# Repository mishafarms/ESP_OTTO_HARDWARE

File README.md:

# OttoDIYESPShield
ESP32 hardware designs for OttoDIY

NOTICE: Most of this has now been verified and works ...

I have created a fusion 360 Otto that has the proper holes in the head for this PCB, I am also including the STL files.
the legs have been modified to use the servos and horns I have.

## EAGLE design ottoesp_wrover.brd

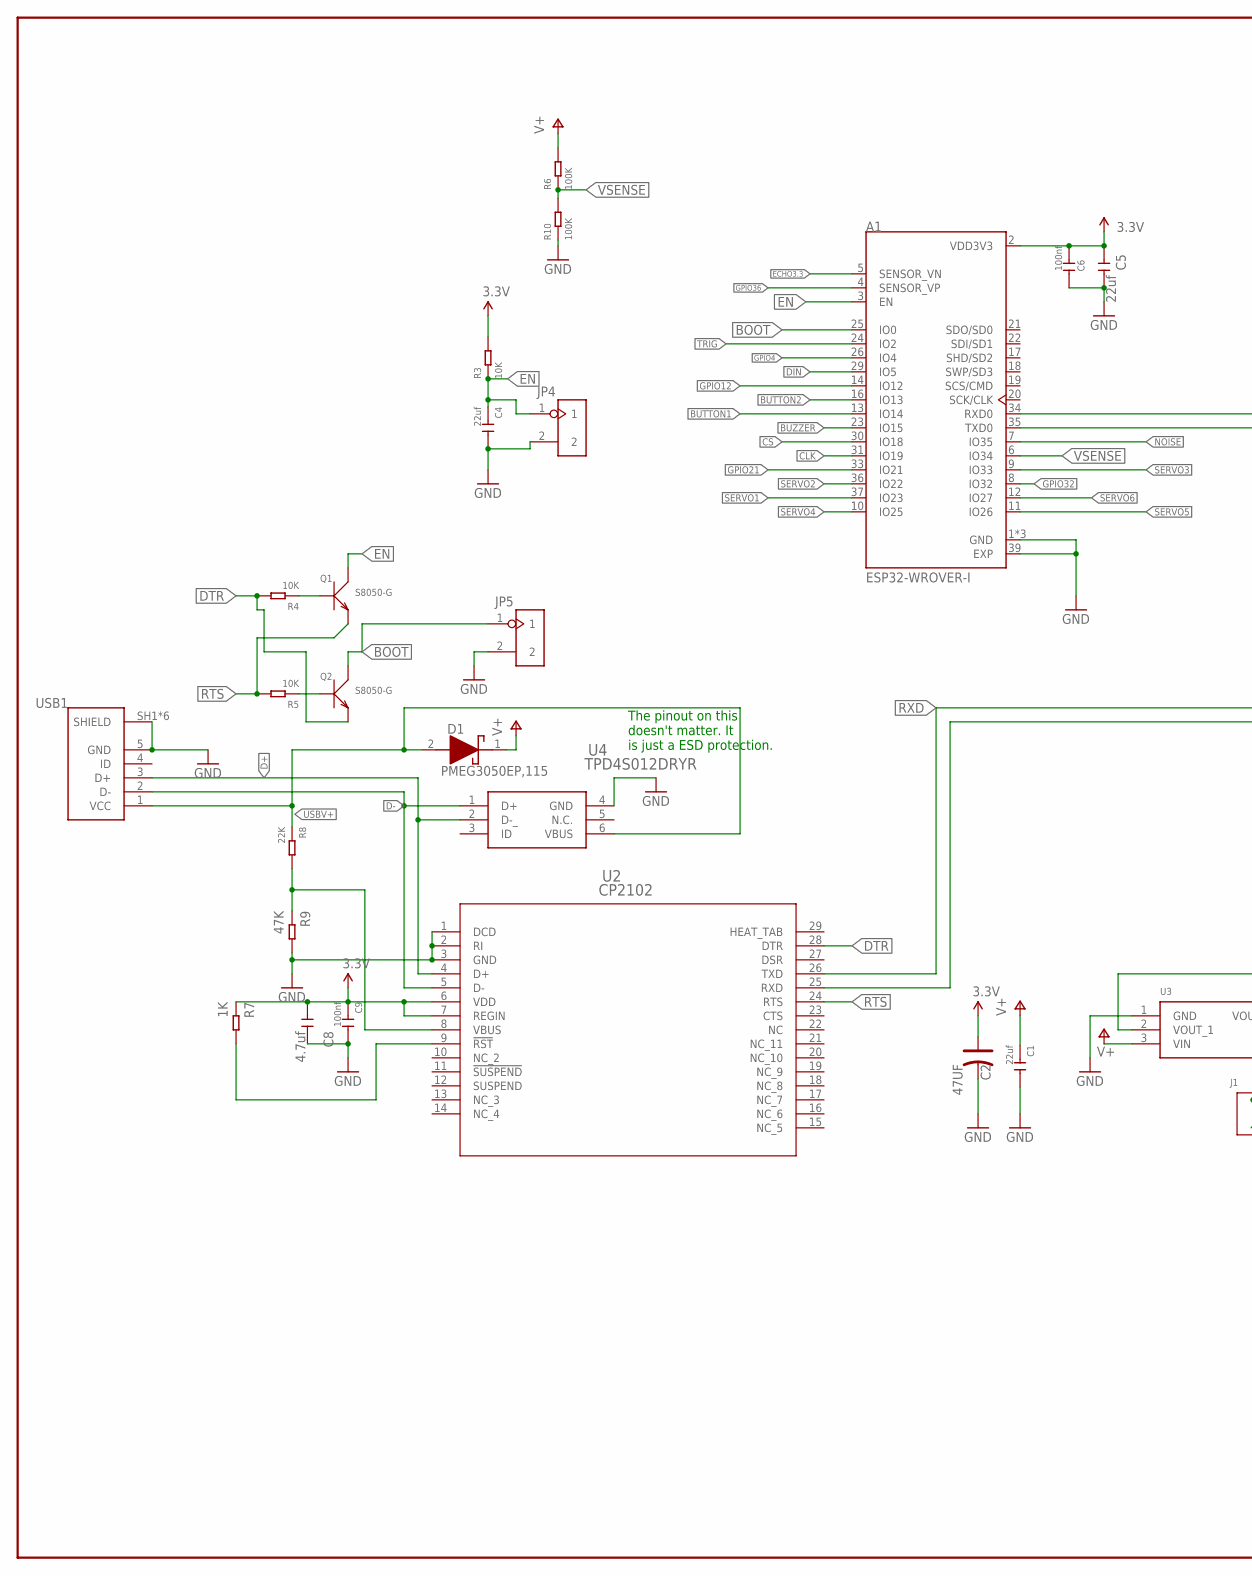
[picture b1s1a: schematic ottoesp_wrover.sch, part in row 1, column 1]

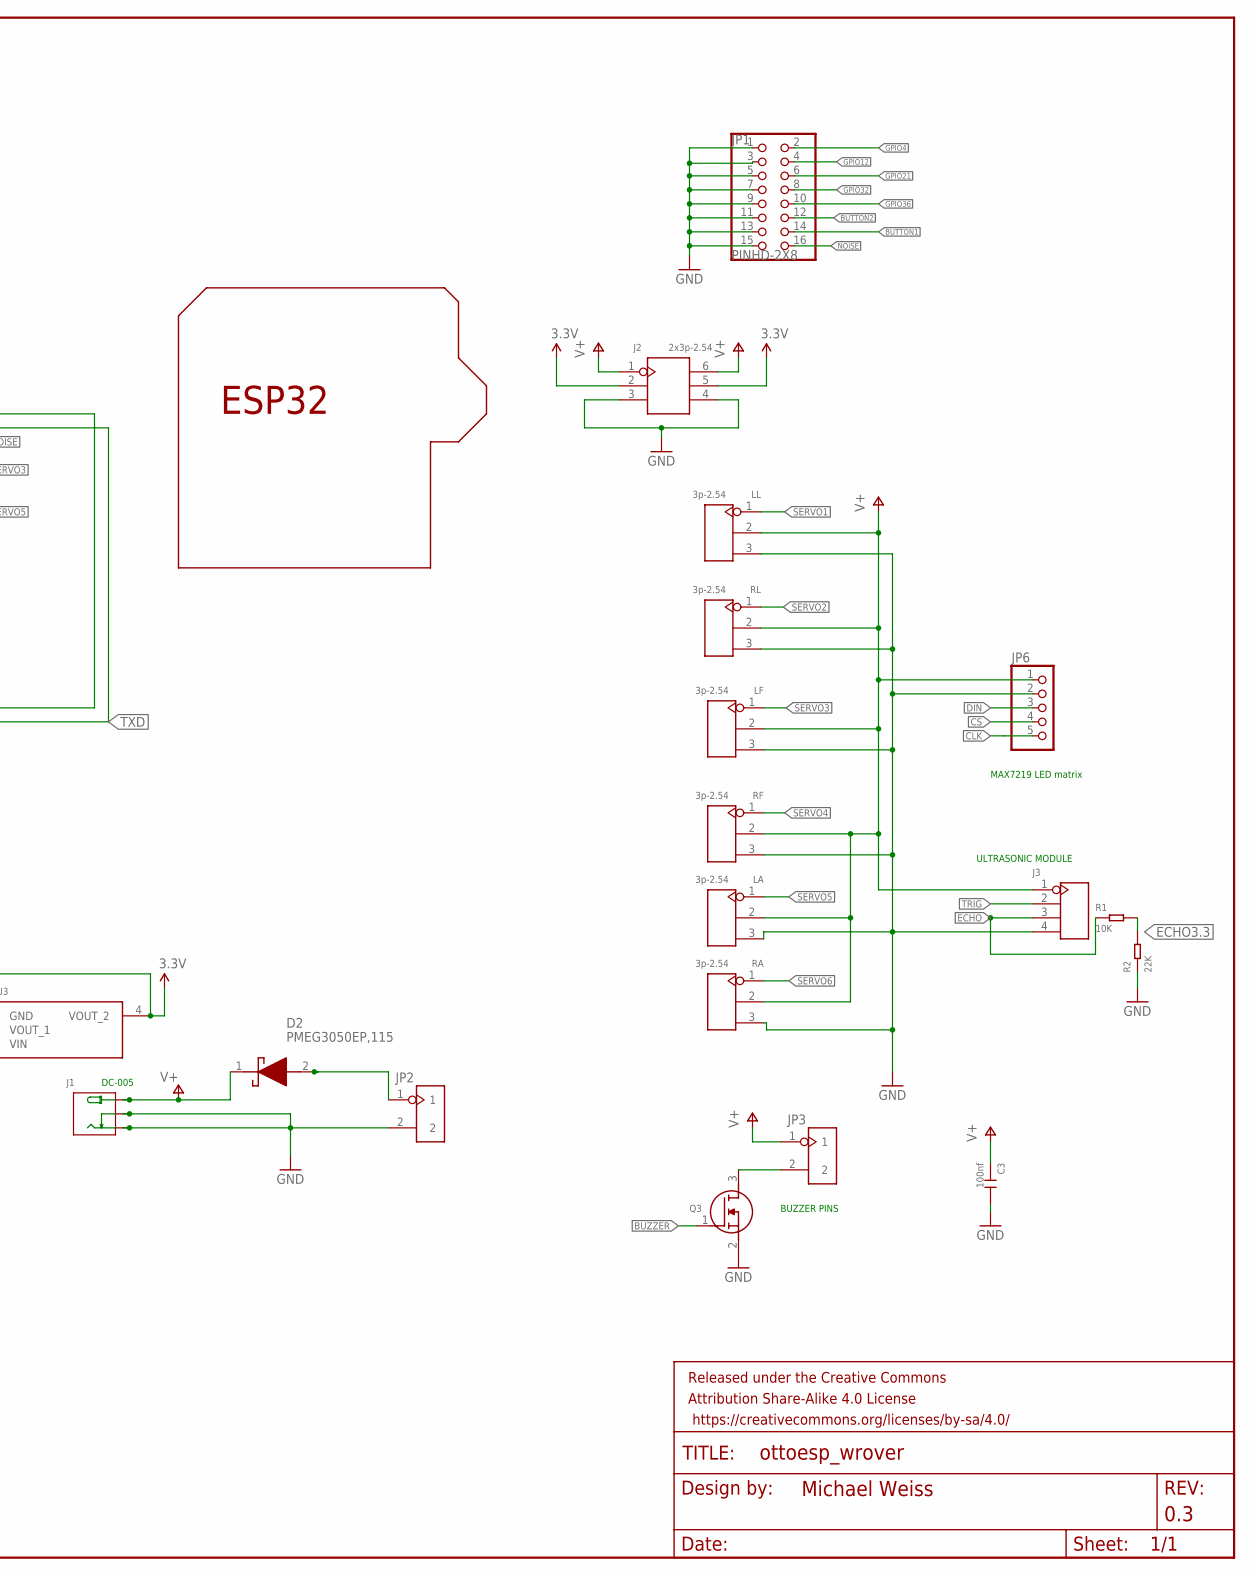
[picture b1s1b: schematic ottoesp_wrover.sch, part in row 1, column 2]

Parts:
A1: ESP32-WROVER-I; XCVR_ESP32-WROVER-I
C1, C4, C5: 22uf; C0805
C2: 47UF; ELECTRO-SMD-C-6MM
C3, C6, C9: 100nf; C0805
C8: 4.7uf; C0805
D1, D2: PMEG3050EP,115; PMEG3050EP115
FRAME1: FRAME-LEDGERMISHAFARMS; MISHAFARMS
J1: DC-005; DCJ3P-14.2X11.0X9.0MM
J2: 2x3p-2.54; H2X3-2.54
J3: 4p-2.54; H4-2.54
JP1: PINHD-2X8; 2X08
JP2, JP3, JP4, JP5: 2p-2.54; H2-2.54
JP6: PINHD-1X5; 1X05
LA: 3p-2.54; H3-2.54
LF: 3p-2.54; H3-2.54
LL: 3p-2.54; H3-2.54
Q1, Q2: S8050-G; SOT-23
Q3: CJ2302; SOT95P230X110-3N
R1, R3, R4, R5: 10K; R0805
R2, R8: 22K; R0805
R6, R10: 100K; R0805
R7: 1K; R0805
R9: 47K; R0805
RA: 3p-2.54; H3-2.54
RF: 3p-2.54; H3-2.54
RL: 3p-2.54; H3-2.54
U2: CP2102; QFN28N5X5-0P5P
U3: CJA1117B-3.3-SOT89; SOT230P700X180-4N
U4: TPD4S012DRYR
U$2: ESP32_SHIELDSMALL; ESP32_ARDUINOSHIELDSMALL
USB1: ZX62-B-5PA; HRS_ZX62-B-5PA(33)

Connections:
3.3V: A1.2 (VDD3V3), C2.+, C5.1, C6.1, C8.1, C9.1, J2.2, J2.5, R3.2, R7.1, U2.6 (VDD), U2.7 (REGIN), U3.2 (VOUT_1), U3.4 (VOUT_2)
BOOT: A1.25 (IO0), JP5.1, Q2.3 (C)
BUTTON1: A1.13 (IO14), JP1.14
BUTTON2: A1.16 (IO13), JP1.12
BUZZER: A1.23 (IO15), Q3.1 (G)
CLK: A1.31 (IO19), JP6.5
CS: A1.30 (IO18), JP6.4
D+: U2.4 (D+), U4.2 (D-_), USB1.3 (D+)
D-: U2.5 (D-), U4.1 (D+), USB1.2 (D-)
DIN: A1.29 (IO5), JP6.3
DTR: Q2.2 (E), R4.2, U2.28 (DTR)
ECHO: J3.3, R1.1
ECHO3.3: A1.5 (SENSOR_VN), R1.2, R2.2
EN: A1.3 (EN), C4.1, JP4.1, Q1.3 (C), R3.1
GND: A1.1 (GND), A1.15 (GND), A1.38 (GND), A1.39 (EXP), C1.2, C2.-, C3.2, C4.2, C5.2, C6.2, C8.2, C9.2, J1.-1B (-), J1.-1T (-), J1.-2 (CDN), J1.-2B (CDN), J2.3, J2.4, J3.4, JP1.1, JP1.3, JP1.5, JP1.7, JP1.9, JP1.11, JP1.13, JP1.15, JP2.2, JP4.2, JP5.2, JP6.2, LA.3, LF.3, LL.3, Q3.2 (S), R2.1, R9.2, R10.1, RA.3, RF.3, RL.3, U2.1 (DCD), U2.2 (RI), U2.3 (GND), U3.1 (GND), U4.4 (GND), USB1.5 (GND), USB1.SH1 (SHIELD), USB1.SH2 (SHIELD), USB1.SH3 (SHIELD), USB1.SH4 (SHIELD), USB1.SH5 (SHIELD), USB1.SH6 (SHIELD)
GPIO4: A1.26 (IO4), JP1.2
GPIO12: A1.14 (IO12), JP1.4
GPIO21: A1.33 (IO21), JP1.6
GPIO32: A1.8 (IO32), JP1.8
GPIO36: A1.4 (SENSOR_VP), JP1.10
unnamed: JP3.2, Q3.3 (D)
unnamed: Q1.1 (B), R4.1
unnamed: Q2.1 (B), R5.1
unnamed: R7.2, U2.9 (!RST)
unnamed: R8.2, R9.1, U2.8 (VBUS)
unnamed: D2.2 (A), JP2.1
NOISE: A1.7 (IO35), JP1.16
RTS: Q1.2 (E), R5.2, U2.24 (RTS)
RXD: A1.34 (RXD0), U2.26 (TXD)
SERVO1: A1.37 (IO23), LL.1
SERVO2: A1.36 (IO22), RL.1
SERVO3: A1.9 (IO33), LF.1
SERVO4: A1.10 (IO25), RF.1
SERVO5: A1.11 (IO26), LA.1
SERVO6: A1.12 (IO27), RA.1
TRIG: A1.24 (IO2), J3.2
TXD: A1.35 (TXD0), U2.25 (RXD)
USBV+: D1.2 (A), R8.1, U4.6 (VBUS), USB1.1 (VCC)
V+: C1.1, C3.1, D1.1 (K), D2.1 (K), J1.+B (+), J1.+T (+), J2.1, J2.6, J3.1, JP3.1, JP6.1, LA.2, LF.2, LL.2, R6.2, RA.2, RF.2, RL.2, U3.3 (VIN)
VSENSE: A1.6 (IO34), R6.1, R10.2

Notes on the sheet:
MAX7219 LED matrix
ULTRASONIC MODULE
BUZZER PINS
The pinout on this doesn't matter. It is just a ESD protection.

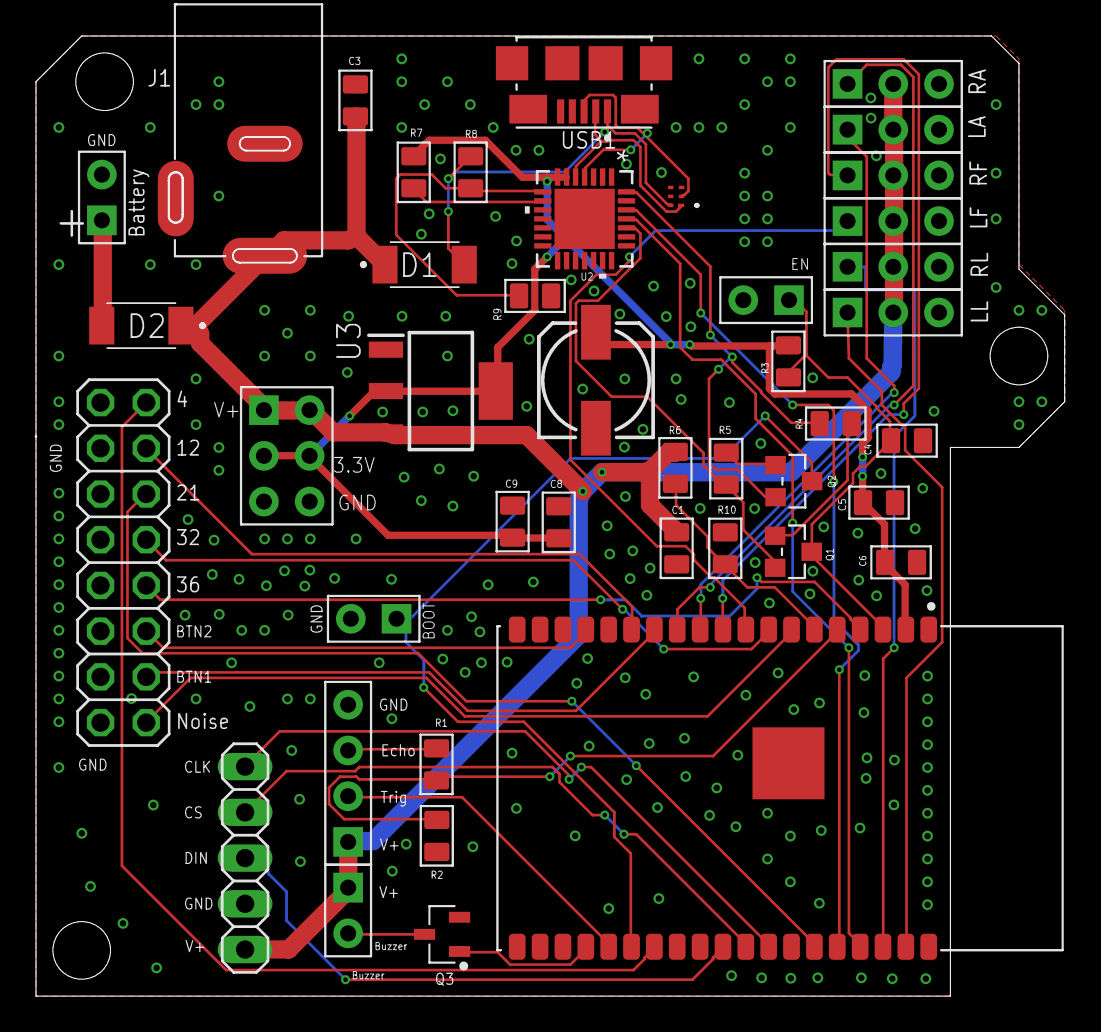
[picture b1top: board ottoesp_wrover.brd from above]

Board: 2 copper layers, 57.2 x 53.3 mm, 45 parts (0 on the bottom side), 40 nets.

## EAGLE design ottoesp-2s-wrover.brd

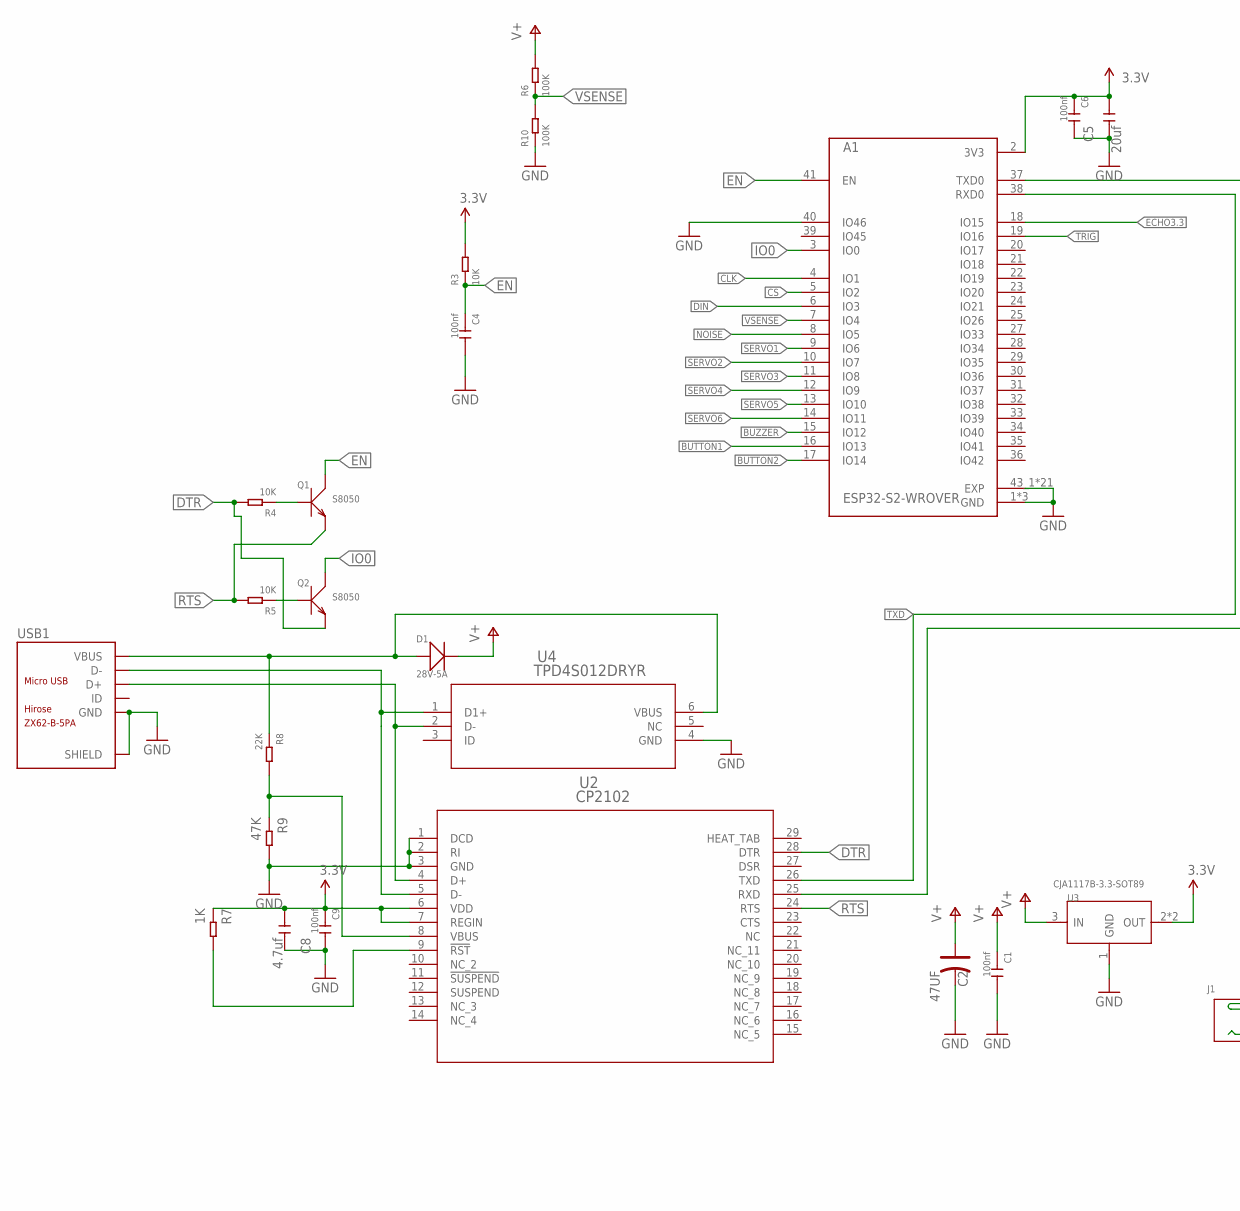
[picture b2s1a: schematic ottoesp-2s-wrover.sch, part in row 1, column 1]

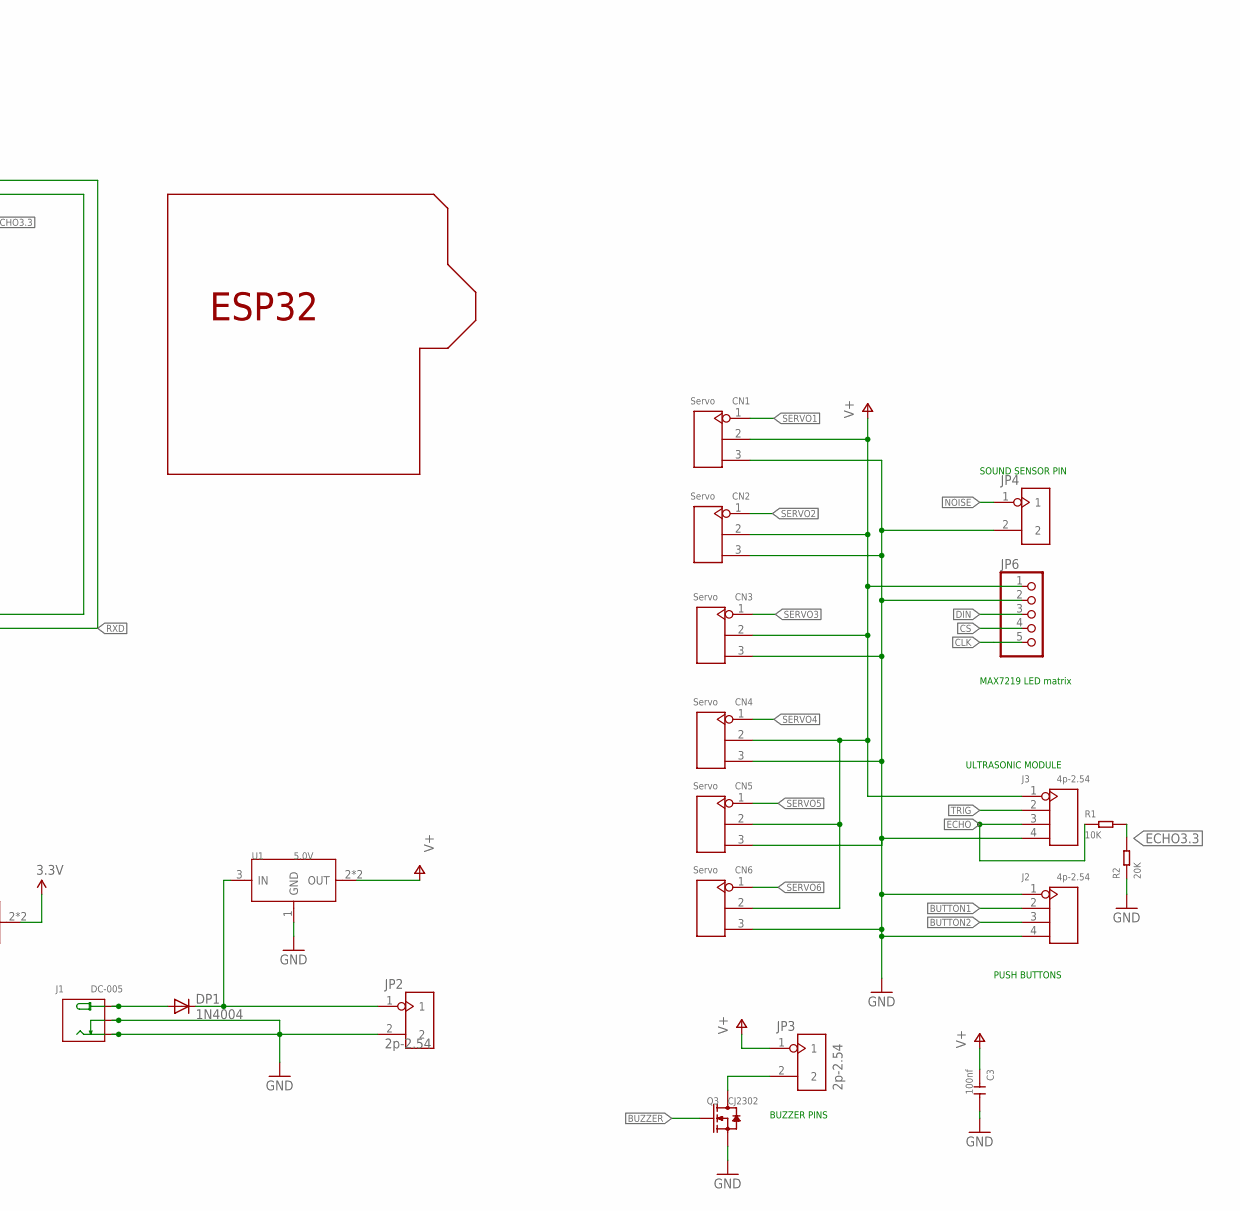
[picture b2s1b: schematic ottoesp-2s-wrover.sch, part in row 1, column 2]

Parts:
A1: ESP32-S2-WROVER; MODULE_ESP32-S2-WROVER
C1, C3, C4, C6, C9: 100nf; C0805
C2: 47UF; ELECTRO-SMD-C-6MM
C5: 20uf; C1206
C8: 4.7uf; C0805
CN1, CN2, CN3, CN4, CN5, CN6: Servo; H3-2.54
D1: 28V-5A; DO-214AA
DP1: 1N4004; DO41-10
J1: DC-005; DCJ3P-14.2X11.0X9.0MM
J2, J3: 4p-2.54; H4-2.54
JP2, JP3, JP4: 2p-2.54; H2-2.54
JP6: PINHD-1X5; 1X05
Q1, Q2: S8050; SOT-23
Q3: CJ2302; SOT-23
R1, R3, R4, R5: 10K; R0805
R2: 20K; R0805
R6, R10: 100K; R0805
R7: 1K; R0805
R8: 22K; R0805
R9: 47K; R0603
U1: 5.0V; SOT-223
U2: CP2102; QFN28N5X5-0P5P
U3: CJA1117B-3.3-SOT89; SOT-89
U4: TPD4S012DRYR; DRY6
U$2: ESP32_SHIELDSMALL; ESP32_ARDUINOSHIELDSMALL
USB1: ZX62-B-5PA; MICRO-USB5+6P-SMD-0.65-AB

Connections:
3.3V: A1.2 (3V3), C5.1, C6.1, C8.1, C9.1, R3.2, R7.1, U2.6 (VDD), U2.7 (REGIN), U3.2 (OUT), U3.4 (OUT)
BUTTON1: A1.16 (IO13), J2.2
BUTTON2: A1.17 (IO14), J2.3
BUZZER: A1.15 (IO12), Q3.1 (G)
CLK: A1.4 (IO1), JP6.5
CS: A1.5 (IO2), JP6.4
DIN: A1.6 (IO3), JP6.3
DTR: Q2.2 (E), R4.2, U2.28 (DTR)
ECHO: J3.3, R1.1
ECHO3.3: A1.18 (IO15), R1.2, R2.2
EN: A1.41 (EN), C4.1, Q1.3 (C), R3.1
GND: A1.1 (GND), A1.26 (GND), A1.40 (IO46), A1.42 (GND), A1.43_1 (EXP), A1.43_2 (EXP), A1.43_3 (EXP), A1.43_4 (EXP), A1.43_5 (EXP), A1.43_6 (EXP), A1.43_7 (EXP), A1.43_8 (EXP), A1.43_9 (EXP), A1.43_10 (EXP), A1.43_11 (EXP), A1.43_12 (EXP), A1.43_13 (EXP), A1.43_14 (EXP), A1.43_15 (EXP), A1.43_16 (EXP), A1.43_17 (EXP), A1.43_18 (EXP), A1.43_19 (EXP), A1.43_20 (EXP), A1.43_21 (EXP), C1.2, C2.-, C3.2, C4.2, C5.2, C6.2, C8.2, C9.2, CN1.3, CN2.3, CN3.3, CN4.3, CN5.3, CN6.3, J1.-1 (-), J1.-2 (CDN), J2.1, J2.4, J3.4, JP2.2, JP4.2, JP6.2, Q3.2 (S), R2.1, R9.2, R10.1, U1.1 (GND), U2.1 (DCD), U2.2 (RI), U2.3 (GND), U3.1 (GND), U4.4 (GND), USB1.5 (GND), USB1.P1 (SHIELD), USB1.P2 (SHIELD), USB1.P3 (SHIELD), USB1.P4 (SHIELD), USB1.P5 (SHIELD), USB1.P6 (SHIELD)
IO0: A1.3 (IO0), Q2.3 (C)
unnamed: JP3.2, Q3.3 (D)
unnamed: Q1.1 (B), R4.1
unnamed: Q2.1 (B), R5.1
unnamed: R7.2, U2.9 (!RST)
unnamed: R8.2, R9.1, U2.8 (VBUS)
unnamed: U2.5 (D-), U4.1 (D1+), USB1.2 (D-)
unnamed: DP1.A, J1.+
unnamed: U2.4 (D+), U4.2 (D-), USB1.3 (D+)
unnamed: DP1.C, JP2.1, U1.3 (IN)
NOISE: A1.8 (IO5), JP4.1
RTS: Q1.2 (E), R5.2, U2.24 (RTS)
RXD: A1.37 (TXD0), U2.25 (RXD)
SERVO1: A1.9 (IO6), CN1.1
SERVO2: A1.10 (IO7), CN2.1
SERVO3: A1.11 (IO8), CN3.1
SERVO4: A1.12 (IO9), CN4.1
SERVO5: A1.13 (IO10), CN5.1
SERVO6: A1.14 (IO11), CN6.1
TRIG: A1.19 (IO16), J3.2
TXD: A1.38 (RXD0), U2.26 (TXD)
V+: C1.1, C2.+, C3.1, CN1.2, CN2.2, CN3.2, CN4.2, CN5.2, CN6.2, D1.-, J3.1, JP3.1, JP6.1, R6.2, U1.2 (OUT), U1.TER (OUT), U3.3 (IN)
VBUS: D1.+, R8.1, U4.6 (VBUS), USB1.1 (VBUS)
VSENSE: A1.7 (IO4), R6.1, R10.2

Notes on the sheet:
MAX7219 LED matrix
ULTRASONIC MODULE
PUSH BUTTONS
SOUND SENSOR PIN
BUZZER PINS

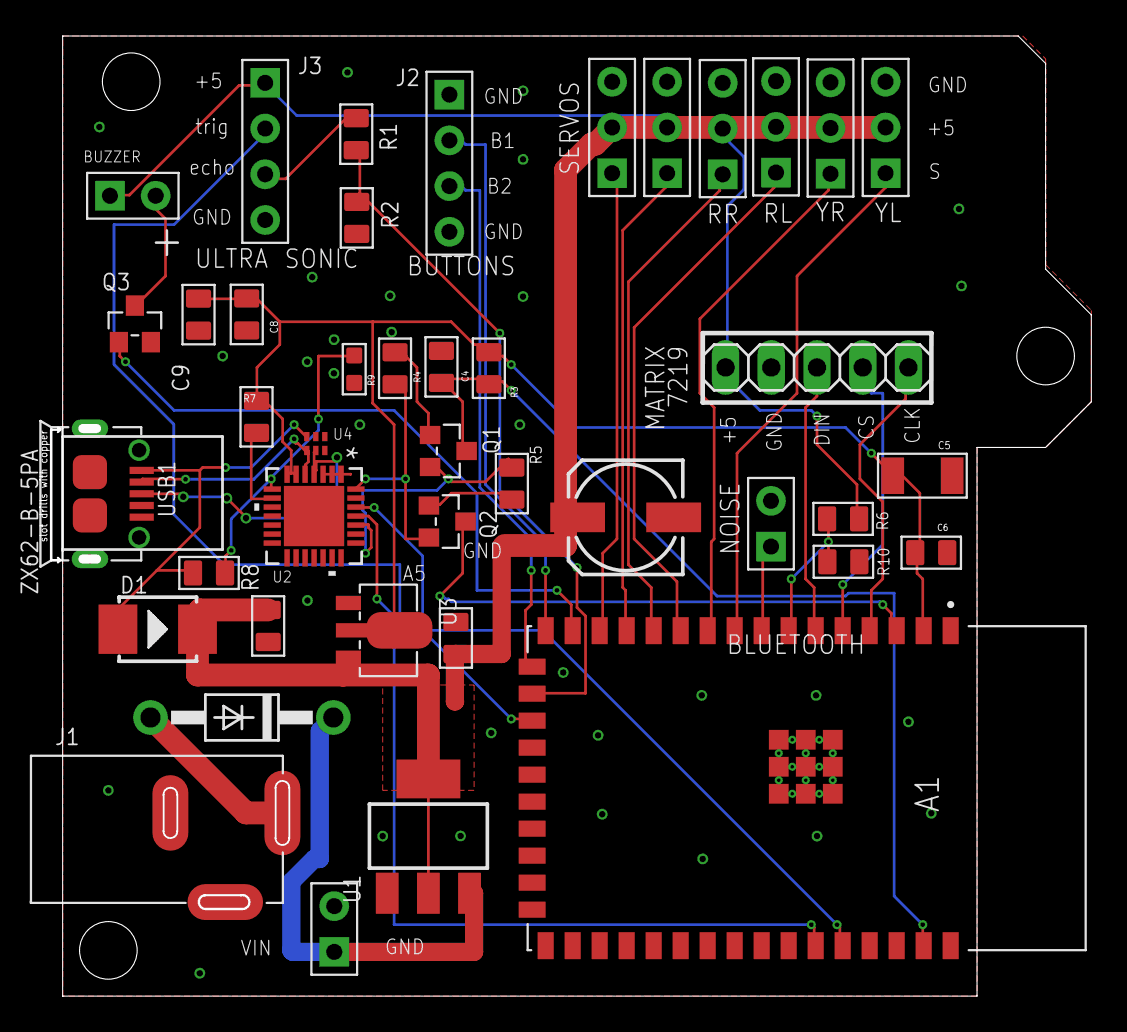
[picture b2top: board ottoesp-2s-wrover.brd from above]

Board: 2 copper layers, 57.8 x 53.3 mm, 43 parts (0 on the bottom side), 36 nets.

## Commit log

2020-09-02 Initial Design
2020-09-02 Create README.md
    Forked from [mishafarms/ESP_OTTO_HARDWARE](https://github.com/mishafarms/ESP_OTTO_HARDWARE)
2020-09-02 Create LICENSE
2020-09-02 The pin names for the Matrix were incorrect
2020-09-04 Adding ESP32-S2 design
2020-09-06 Moved pins to allow a better PCB routing. Fixed all DRC errors.
2020-09-08 Updated to use parts I can find at mouser. Used a higher power 3.3V regulator. Added Gerber zip that I used to order prototype boards from SEEED.
2020-09-09 .gitignore all the files that eagle creates that we don't want uploaded. Added the BOM in CSV (this is the BOM from Mouser) Changed a 20K resistor to 22K so that we don't need some many different res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
2020-10-12 The latest schematic and board layout
2020-10-12 new pictures
2020-10-13 Added pins with V+, 3.3V, and GND for expansion
2020-10-15 Changed some pin usage to give us as many extra I/O pins as possible. Added an EN and a BOOT jumper, so we can boot and load in emergency. Moved headers and changed some cap values.
2020-10-15 changed the name of the gerber file
2020-10-15 changed the name of the schematic and board
2020-12-01 Updated cap. These have been produced and seem to work. Still testing
2020-12-01 Added esp32_shield as new brain_type. A little tight. But a good start
2020-12-02 Moved the power and usb holes a little and increased the size a little.
2020-12-15 Changed to bew PCB with cutout on corner changed cap to 22uf
2020-12-15 Moved the servo pins and some others closer together to allow the use of pin strips.
2020-12-15 Latest version
2020-12-27 Latest board with 3d packages
2020-12-27 Fusion 360 files and image
2020-12-27 Latest part list with mouser part #s
2020-12-27 latest eagle file
2020-12-27 STL files

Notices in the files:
parts and their libraries:
SparkFun-Aesthetics: Licensing: Creative Commons ShareAlike 4.0 International - https://creativecommons.org/licenses/by-sa/4.0
SamacSys_Parts: Released under the Creative Commons Attribution Share-Alike 4.0 License
SamacSys_Parts: https://creativecommons.org/licenses/by-sa/4.0
